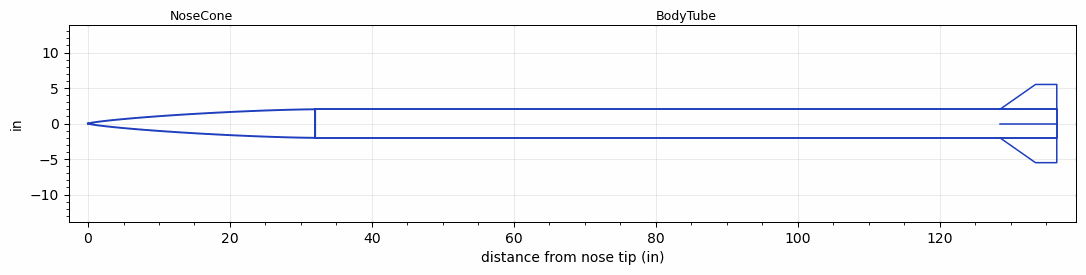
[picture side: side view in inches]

<RASAeroDocument>
 <FileVersion>2</FileVersion>
 <RocketDesign>
  <NoseCone>
   <Length>32</Length>
   <Diameter>4.02</Diameter>
   <Shape>Von Karman Ogive</Shape>
   <Location>0</Location>
  </NoseCone>
  <BodyTube>
   <Length>104.5</Length>
   <Diameter>4.02</Diameter>
   <Location>32</Location>
   <Fin>
    <Count>4</Count>
    <Chord>8</Chord>
    <Span>3.5</Span>
    <SweepDistance>5</SweepDistance>
    <TipChord>3</TipChord>
    <Thickness>0.25</Thickness>
    <Location>8</Location>
    <AirfoilSection>Hexagonal Blunt Base</AirfoilSection>
    <FX1>0.7469705</FX1>
   </Fin>
   <Protuberance>
    <StreamlinedNoBaseDrag>0.3693967</StreamlinedNoBaseDrag>
    <StreamlinedWithBaseDrag>0</StreamlinedWithBaseDrag>
    <InclinedPlate1Angle>0</InclinedPlate1Angle>
    <InclinedPlate1FrontalArea>0</InclinedPlate1FrontalArea>
    <InclinedPlate2Angle>0</InclinedPlate2Angle>
    <InclinedPlate2FrontalArea>0</InclinedPlate2FrontalArea>
   </Protuberance>
  </BodyTube>
  <Surface>Rough Camouflage Paint</Surface>
  <ModifiedBarrowman>False</ModifiedBarrowman>
  <Turbulence>False</Turbulence>
  <UseBooster1>False</UseBooster1>
  <UseBooster2>False</UseBooster2>
  <Comments>Iris constant-diameter sustainer finned</Comments>
 </RocketDesign>
 <LaunchSite>
  <Altitude>0</Altitude>
  <Pressure>29.9214</Pressure>
  <RodAngle>0</RodAngle>
  <RodLength>3.2808</RodLength>
  <Temperature>59</Temperature>
  <WindSpeed>4.4739</WindSpeed>
 </LaunchSite>
 <Recovery>
  <Altitude1>0</Altitude1>
  <Altitude2>0</Altitude2>
  <DeviceType1>None</DeviceType1>
  <DeviceType2>None</DeviceType2>
  <Event1>False</Event1>
  <Event2>False</Event2>
  <Size1>0</Size1>
  <Size2>0</Size2>
  <EventType1>None</EventType1>
  <EventType2>None</EventType2>
  <CD1>0</CD1>
  <CD2>0</CD2>
 </Recovery>
</RASAeroDocument>
